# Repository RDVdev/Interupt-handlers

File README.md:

# Interupt-handlers
Esw project
Topic:- LoRaWAN

Members-
- Tatva 
- Aryan
- Priyanka
- Devansh

Guide-
- Aftab hussain

TA-
- Ruthwik

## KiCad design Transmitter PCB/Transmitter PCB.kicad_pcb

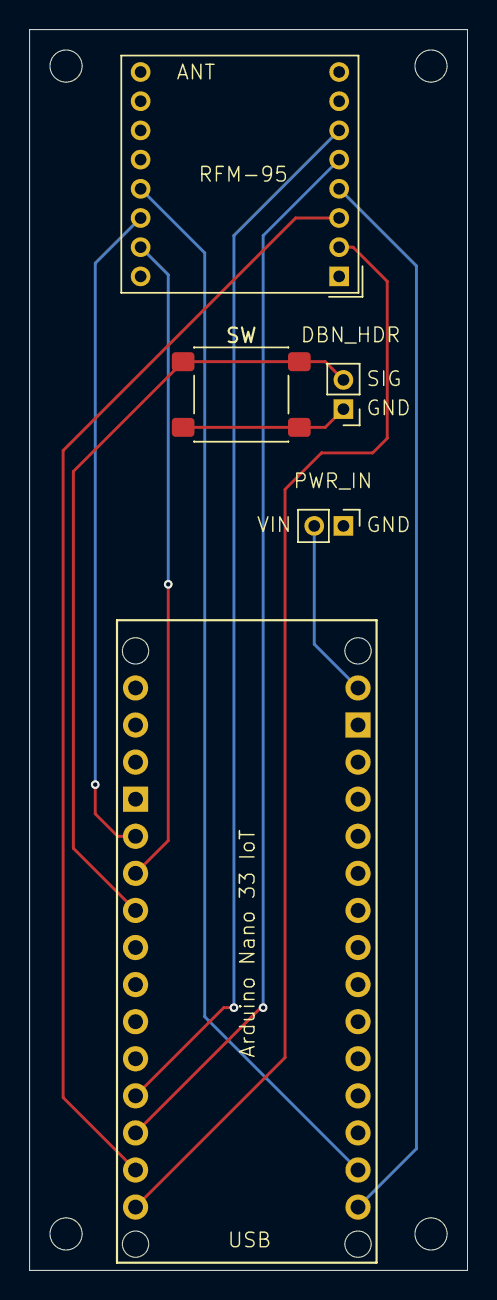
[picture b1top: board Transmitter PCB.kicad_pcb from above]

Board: 2 copper layers, 30.0 x 85.0 mm, 5 parts (0 on the bottom side), 11 nets.

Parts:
A1: Arduino_Nano_33_IoT_Socket
J1: PWR_IN; PinHeader_1x02_P2.00mm_Vertical
J2: DBN_HDR; PinHeader_1x02_P2.00mm_Vertical
SW: TX_BTN; SW_SPST_PTS645Sx43SMTR92
U1: RFM95W-868S2; HOPERF_RFM9XW_THT

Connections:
+3.3V: A1.3V3 (3.3V), U1.13 (3.3V)
GND: A1.GND1 (GND), A1.GND2 (GND), J1.1, J2.1, SW.2, U1.1 (GND), U1.8 (GND), U1.10 (GND)
unnamed: A1.D11 (D11_MOSI), U1.3 (MOSI)
unnamed: A1.D12 (D12_MISO), U1.2 (MISO)
unnamed: A1.D13 (D13_SCK), U1.4 (SCK)
unnamed: A1.D4, J2.2, SW.1
unnamed: A1.D2, U1.14 (DIO0)
unnamed: A1.D3, U1.15 (DIO1)
unnamed: A1.D10, U1.5 (NSS)
unnamed: A1.D9, U1.6 (RESET)
VCC: A1.VIN, J1.2

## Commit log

2025-08-11 readme
2025-09-15 first transmitter reciver
2025-09-15 Corrected Folder Structure
2025-09-15 Changed code
2025-09-15 Correct folder name
2025-09-15 Added sample server code
2025-09-15 Made changes to the backend
2025-09-29 power
2025-09-29 seq update
2025-09-29 Added debouncing to button
2025-10-06 Stuff changed
2025-10-11 arduino code
2025-10-11 New App.py
2025-10-11 Fixed issue
2025-10-11 PCB Design and gitignore
2025-10-11 tatva🥵🙏
2025-10-11 Added fabric based auto deployment setup
2025-10-13 Updated server codes
2025-11-15 Updated app
2025-11-15 added load and delete
2025-11-17 updated codes without serial commands
2025-11-19 enclosure docs
2025-12-01 iiit wifi
